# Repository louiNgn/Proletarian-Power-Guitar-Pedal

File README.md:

# Proletarian Power Guitar pedal
## an open sourced, ancom-themed overdrive guitar pedal.

This was an incredibly scuffed attempt at making an electric guitar pedal as a way to learn and document my electrical engineering journey as a creator.

The really crappy pedal was very loosely based off of the tube-screamer schematic, with a notable addition of a hard-clipping switch, or as I like to call it, the fun switch.

[PCB](PCB) folder contains the kicad files

[production](production) contains the gerber files for sending to your favorite PCB manufacturer

[Acrylic_Shields](Acrylic_Shields) contain the STL and .f3d files to the acrylic plates for fixing switches and shield the PCB from the ground.

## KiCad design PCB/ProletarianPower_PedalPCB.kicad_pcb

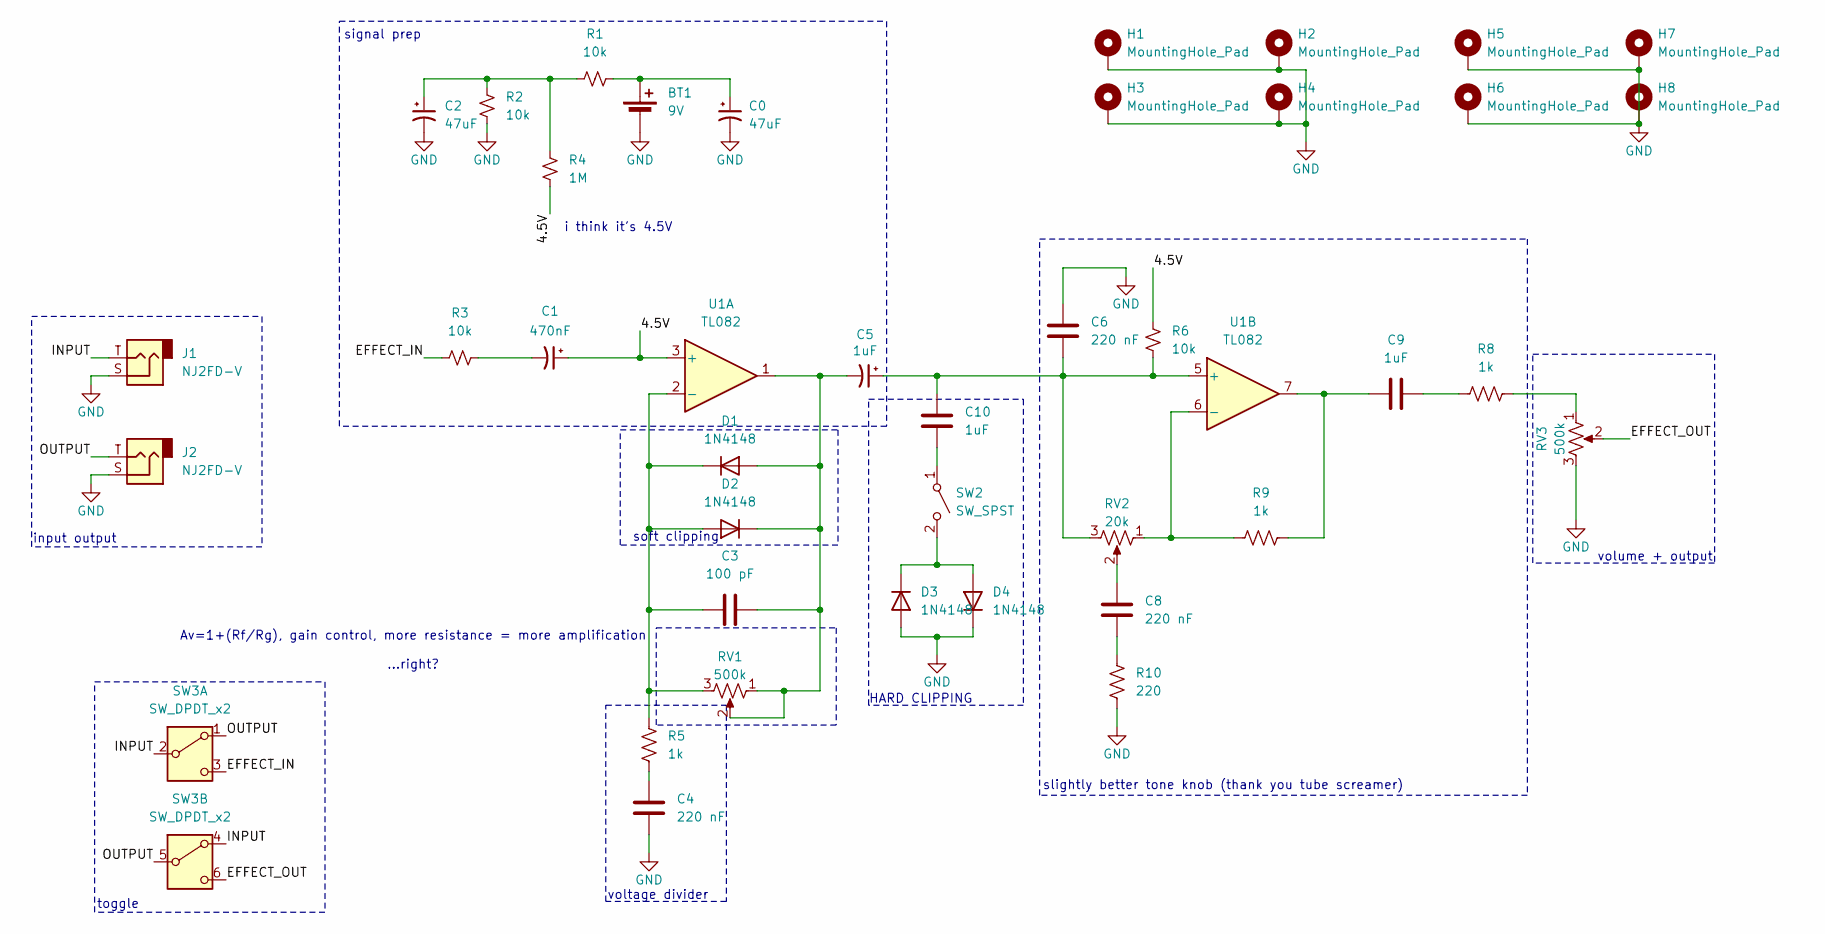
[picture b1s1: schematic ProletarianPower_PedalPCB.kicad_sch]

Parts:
BT1: 9V; Barrel_Jack_PTH
C0, C2: 47uF; CP_Radial_D4.0mm_P2.00mm; Voltage 35V; Tolerance 20%
C1: 470nF; CP_Radial_D5.0mm_P2.00mm; Voltage 470nF; Tolerance 100%
C3: 100 pF; C_Axial_L5.1mm_D3.1mm_P7.50mm_Horizontal
C4, C6, C8: 220 nF; C_Axial_L5.1mm_D3.1mm_P7.50mm_Horizontal
C5: 1uF; CP_Radial_D4.0mm_P2.00mm; Voltage 1uF; Tolerance 100%
C9, C10: 1uF; C_Axial_L5.1mm_D3.1mm_P7.50mm_Horizontal
D1, D2, D3, D4: 1N4148; D_DO-35_SOD27_P7.62mm_Horizontal
H1, H2, H3, H4: MountingHole_Pad; MountingHole_3.2mm_M3_DIN965_Pad_TopBottom
H5, H6, H7, H8: MountingHole_Pad; MountingHole_2.2mm_M2_DIN965_Pad_TopBottom
J1, J2: NJ2FD-V; Jack_6.35mm_Neutrik_NMJ4HFD2_Horizontal
R1, R2, R3, R6: 10k; R_Axial_DIN0207_L6.3mm_D2.5mm_P7.62mm_Horizontal
R4: 1M; R_Axial_DIN0207_L6.3mm_D2.5mm_P7.62mm_Horizontal
R5, R8, R9: 1k; R_Axial_DIN0207_L6.3mm_D2.5mm_P7.62mm_Horizontal
R10: 220; R_Axial_DIN0207_L6.3mm_D2.5mm_P7.62mm_Horizontal
RV1, RV3: 500k; Potentiometer_Alps_RK09K_Single_Vertical
RV2: 20k; Potentiometer_Alps_RK09K_Single_Vertical
SW2: SW_SPST; SolderWire-0.127sqmm_1x02_P3.7mm_D0.48mm_OD1mm
SW3: SW_DPDT_x2; SW_CK_JS202011CQN_DPDT_Straight
U1: TL082; SMDIP-8_W7.62mm

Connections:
/4.5V: C1.1, R4.2, R6.2, U1.3 (+)
/EFFECT_IN: R3.1, SW3.3 (C)
/EFFECT_OUT: RV3.2, SW3.6 (C); also elsewhere on the board
/INPUT: J1.T, SW3.2 (B), SW3.4 (A)
/OUTPUT: J2.T, SW3.1 (A), SW3.5 (B)
GND: BT1.2 (-), C0.2, C2.2, C4.2, C6.1, D3.2 (A), D4.1 (K), H1.1 (1_1), H2.1 (1_1), H3.1 (1_1), H4.1 (1_1), H5.1 (1_1), H6.1 (1_1), H7.1 (1_1), H8.1 (1_1), J1.S, J2.S, R2.1, R10.1, RV3.3; also elsewhere on the board
unnamed: BT1.1 (+), C0.1, R1.2
unnamed: C1.2, R3.2
unnamed: C2.1, R1.1, R2.2, R4.1
unnamed: C4.1, R5.2
unnamed 10: C8.1, RV2.2; also elsewhere on the board
unnamed: C8.2, R10.2
unnamed: C9.1, R9.2, U1.7
unnamed: C9.2, R8.1
unnamed 14: C3.1, C5.2, D1.2 (A), D2.1 (K), RV1.1, RV1.2, U1.1; also elsewhere on the board
unnamed 15: C3.2, D1.1 (K), D2.2 (A), R5.1, RV1.3, U1.2 (-); also elsewhere on the board
unnamed 16: D3.1 (K), D4.2 (A), SW2.2 (B); also elsewhere on the board
unnamed 17: R8.2, RV3.1; also elsewhere on the board
unnamed 18: C10.2, SW2.1 (A); also elsewhere on the board
unnamed 19: C5.1, C6.2, C10.1, R6.1, RV2.3, U1.5 (+); also elsewhere on the board
unnamed 20: R9.1, RV2.1, U1.6 (-); also elsewhere on the board

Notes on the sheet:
input output
volume + output
i think it's 4.5V
HARD CLIPPING
voltage divider
signal prep
soft clipping
toggle
Av=1+(Rf/Rg), gain control, more resistance = more amplification ...right?
slightly better tone knob (thank you tube screamer)

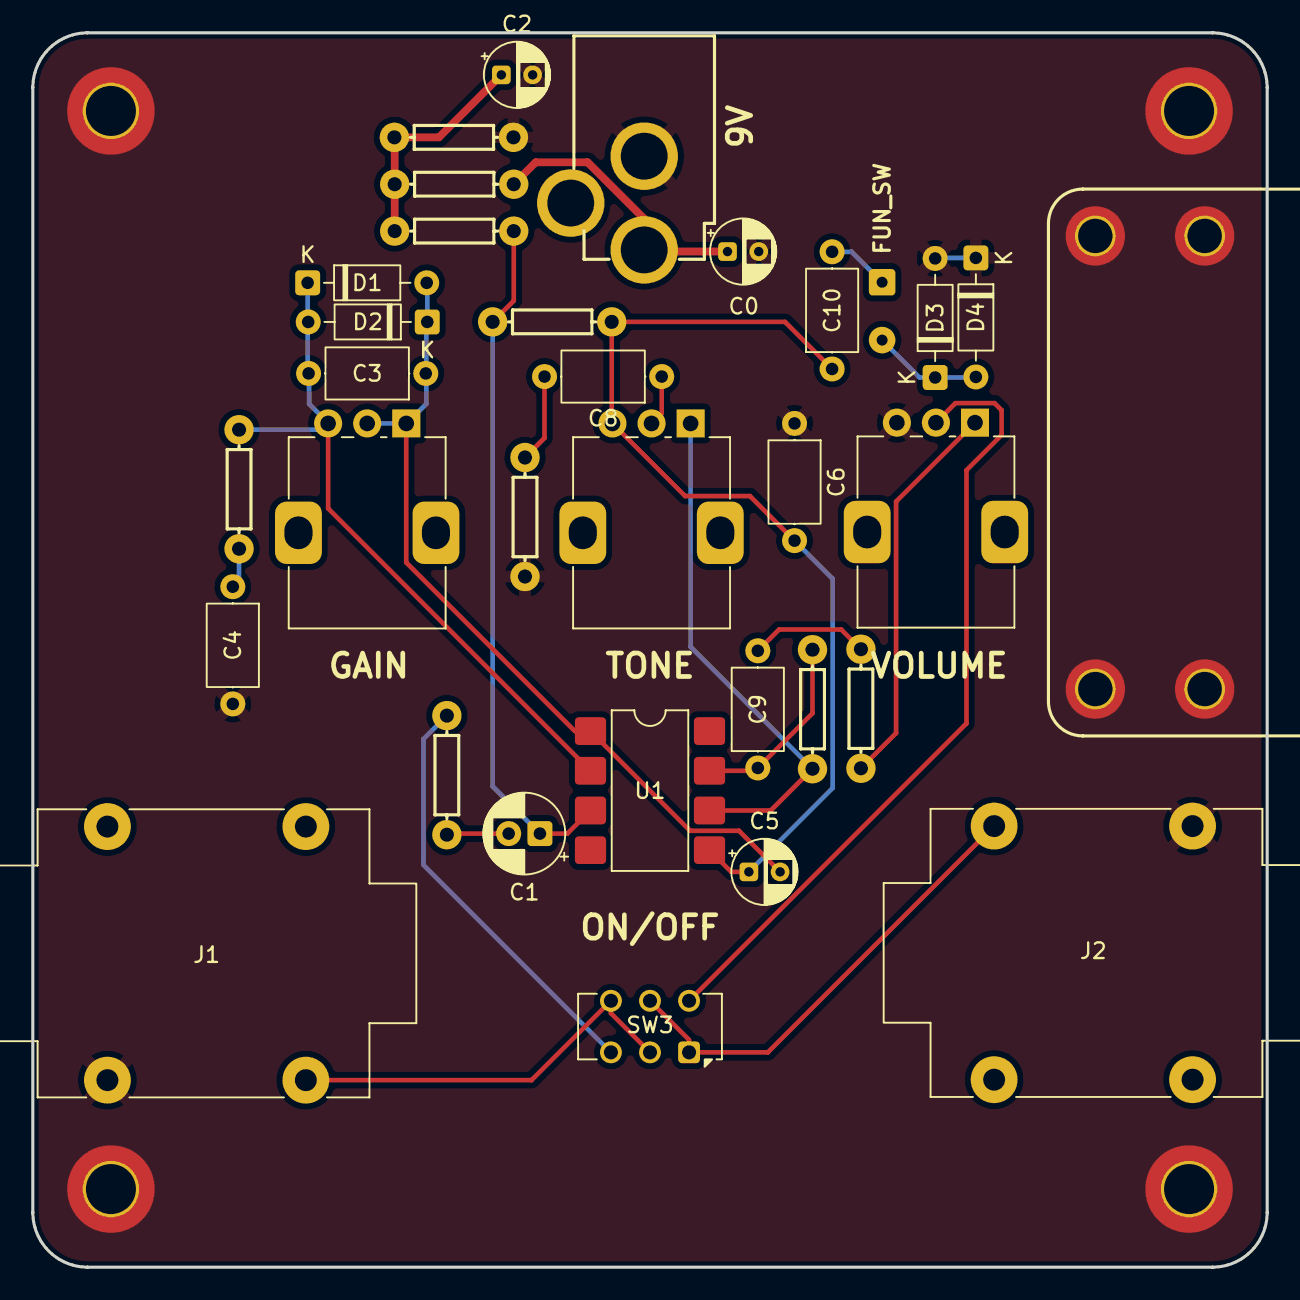
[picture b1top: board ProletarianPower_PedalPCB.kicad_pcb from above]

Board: 2 copper layers, 79.0 x 79.0 mm, 40 parts (0 on the bottom side), 21 nets.

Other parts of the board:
FUN_SW: SW_SPST; SolderWire-0.127sqmm_1x02_P3.7mm_D0.48mm_OD1mm
GAIN: 500k; Potentiometer_Alps_RK09K_Single_Vertical
TONE: 20k; Potentiometer_Alps_RK09K_Single_Vertical
VOLUME: 500k; Potentiometer_Alps_RK09K_Single_Vertical

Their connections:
/EFFECT_OUT: VOLUME.2; also elsewhere on the board
GND: VOLUME.3; also elsewhere on the board
unnamed 10: TONE.2; also elsewhere on the board
unnamed 14: GAIN.1, GAIN.2; also elsewhere on the board
unnamed 15: GAIN.3; also elsewhere on the board
unnamed 16: FUN_SW.2 (B); also elsewhere on the board
unnamed 17: VOLUME.1; also elsewhere on the board
unnamed 18: FUN_SW.1 (A); also elsewhere on the board
unnamed 19: TONE.3; also elsewhere on the board
unnamed 20: TONE.1; also elsewhere on the board
